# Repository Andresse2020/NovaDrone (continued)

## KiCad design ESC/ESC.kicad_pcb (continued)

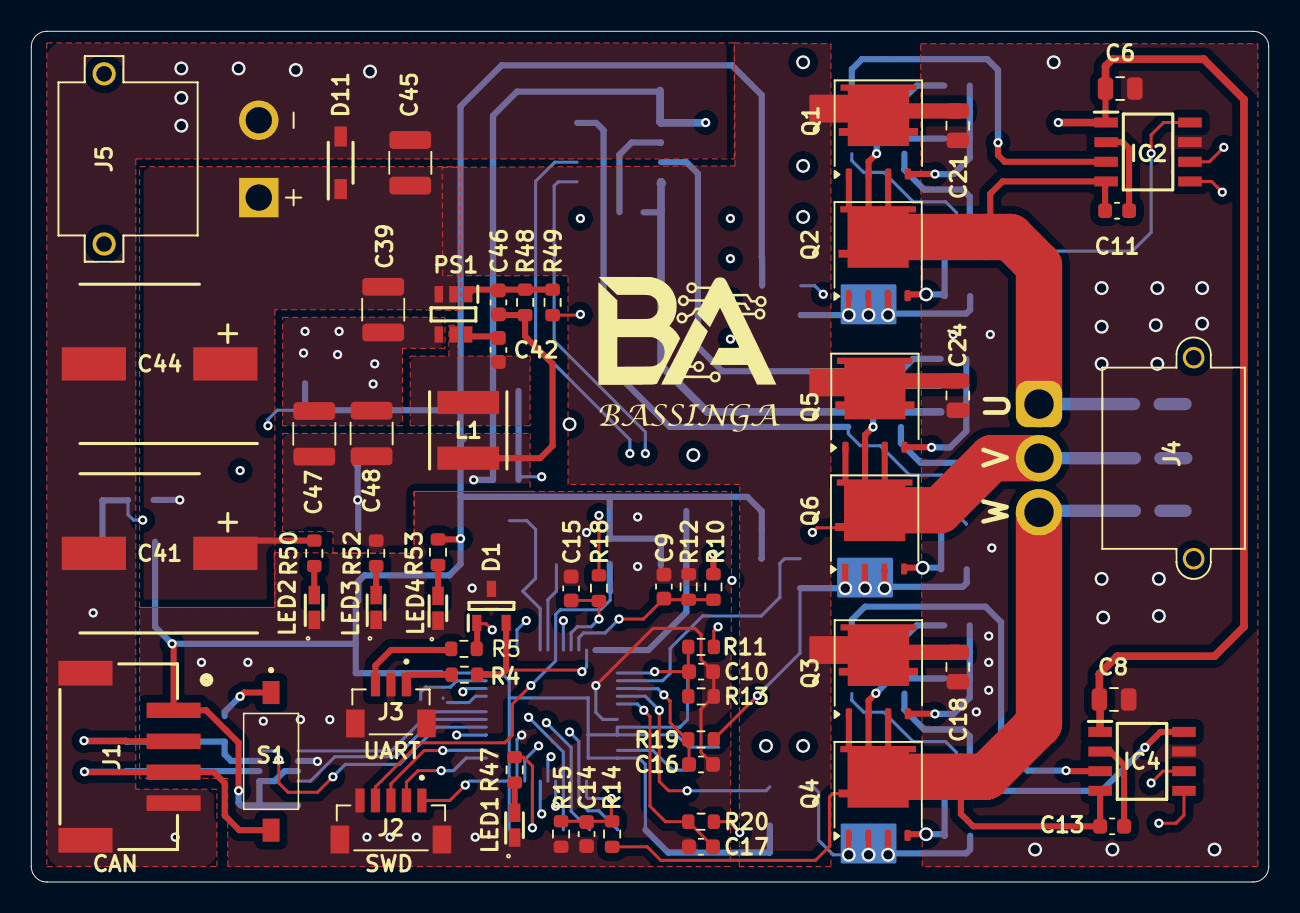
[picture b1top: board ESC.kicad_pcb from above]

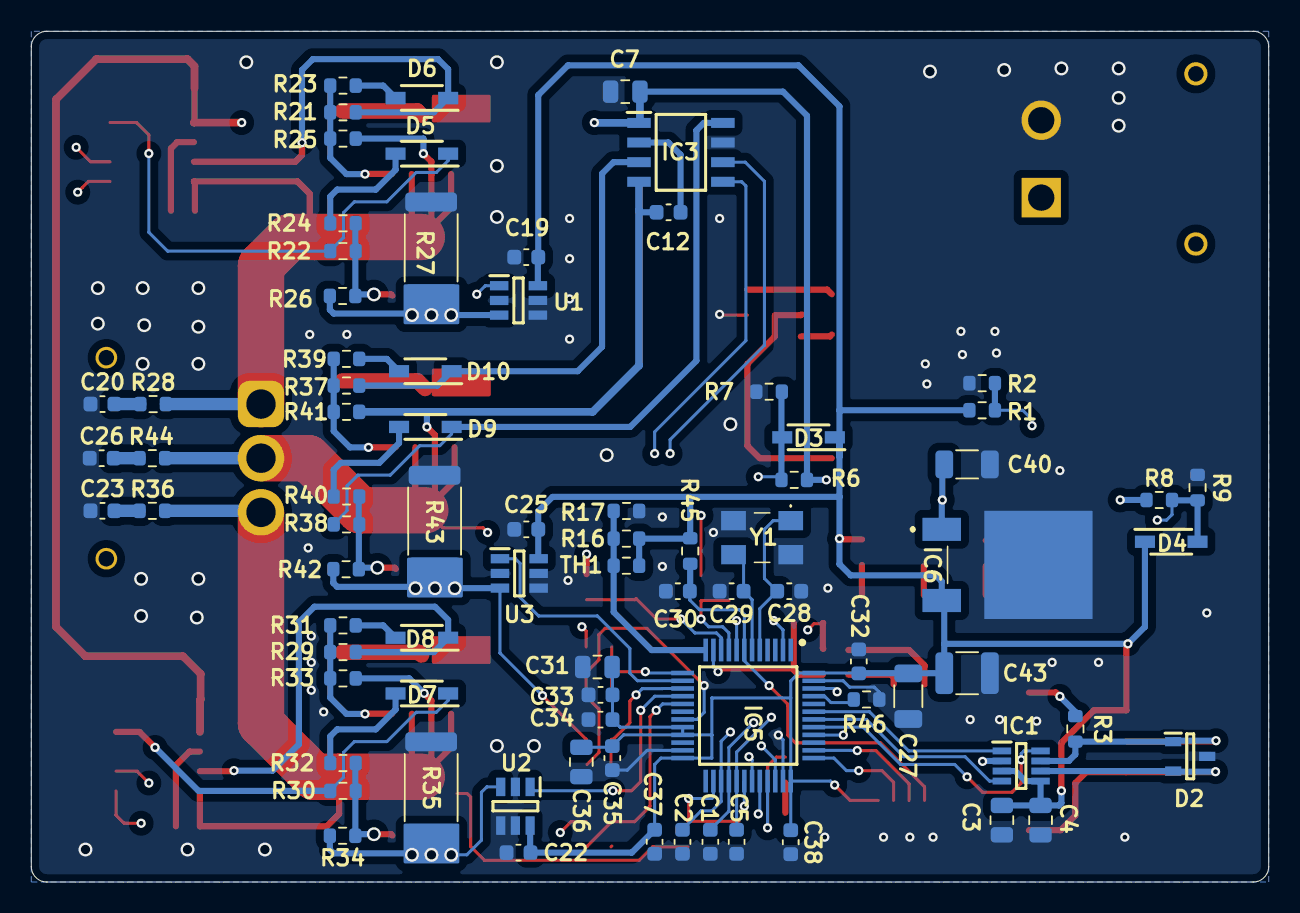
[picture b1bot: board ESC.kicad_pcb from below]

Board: 4 copper layers, 80.0 x 55.0 mm, 140 parts (80 on the bottom side), 77 nets.

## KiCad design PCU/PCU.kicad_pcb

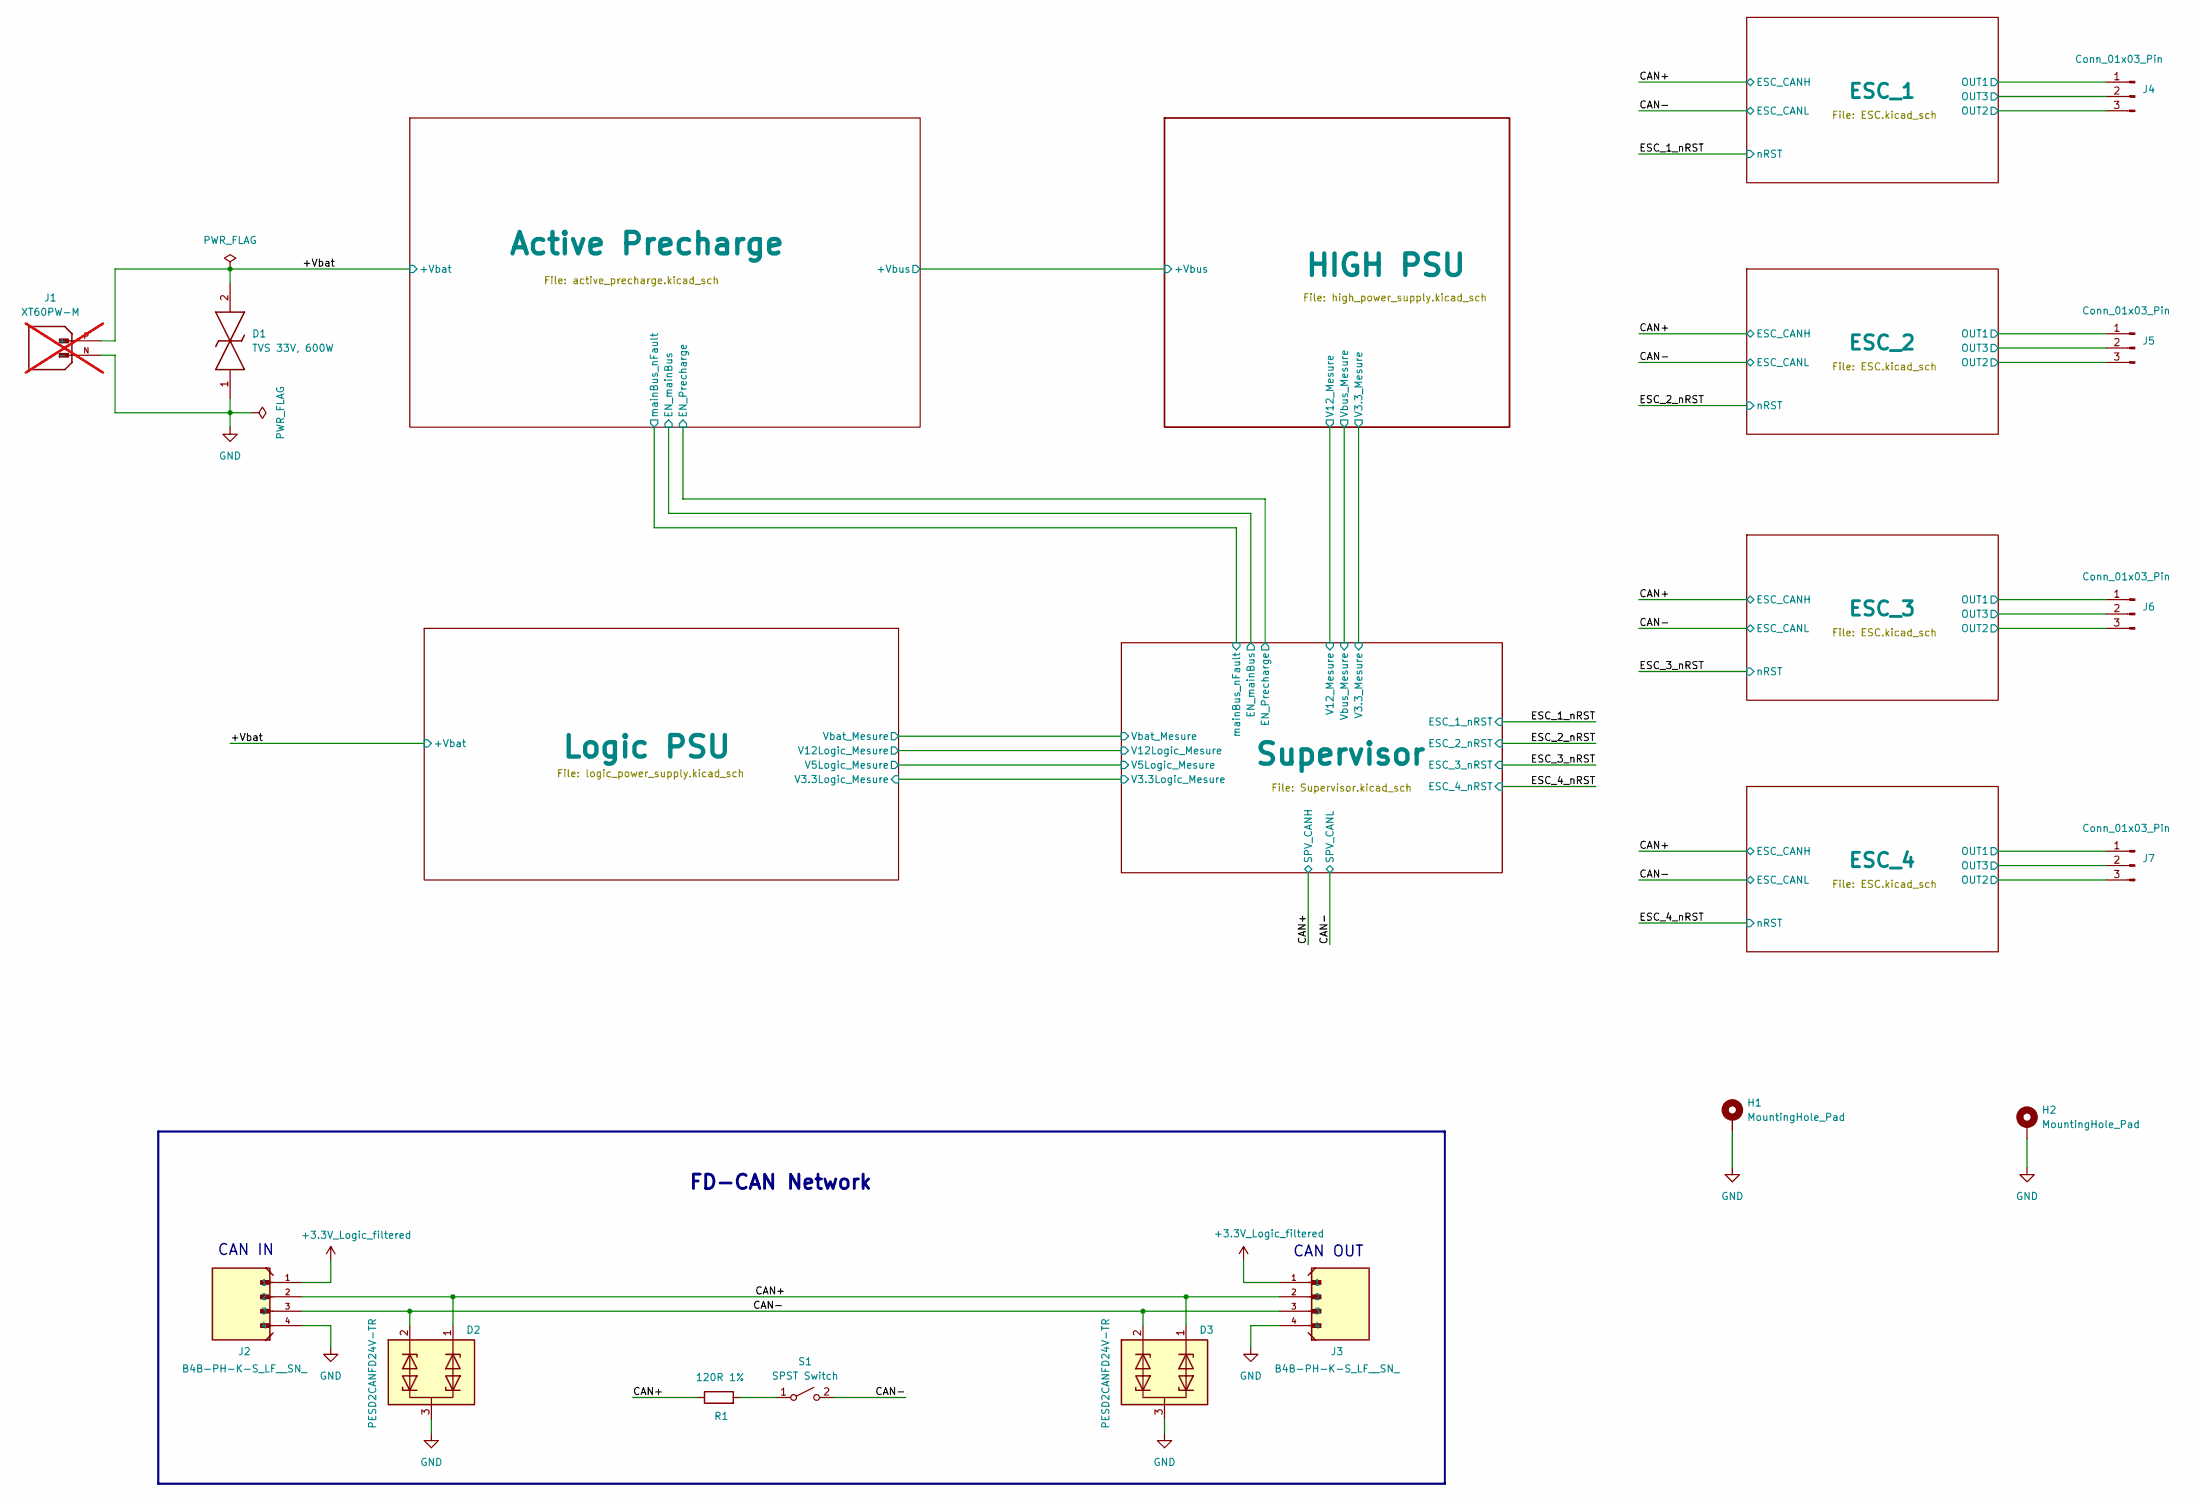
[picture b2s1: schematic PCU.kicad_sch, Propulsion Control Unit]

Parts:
D1: TVS 33V, 600W; DIONM5436X244N; Mouser Part Number 652-SMBJ33CA
D2, D3: PESD2CANFD24V-TR; SOT95P230X110-3N; Mouser Part Number 771-PESD2CANFD24V-TR
H1, H2: MountingHole_Pad; MountingHole_2.2mm_M2_DIN965_Pad
J1: XT60PW-M; AMASS_XT60PW-M; PARTREV V1.2; not fitted
J2, J3: B4B-PH-K-S_LF__SN_; JST_B4B-PH-K-S_LF__SN_
J4, J5, J6, J7: Conn_01x03_Pin; SolderWire-0.75sqmm_1x03_P4.8mm_D1.25mm_OD2.3mm
R1: 120R 1%; R_0603_1608Metric; Manufacturer_Part_Number AC0603FR-07120RL
S1: SPST Switch; DS04254201BKSMT; Mouser Part Number 490-DS04254201BK-SMT

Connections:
+3.3V_Logic_filtered: J2.1, J3.1; also elsewhere on the board
/+Vbat: D1.2, J1.P (+); also elsewhere on the board
/CAN+: D2.1, D3.1, J2.2, J3.2, R1.1; also elsewhere on the board
/CAN-: D2.2, D3.2, J2.3, J3.3, S1.2; also elsewhere on the board
/ESC_1/OUT1: J4.1; also elsewhere on the board
/ESC_1/OUT2: J4.3; also elsewhere on the board
/ESC_1/OUT3: J4.2; also elsewhere on the board
/ESC_2/OUT1: J5.1; also elsewhere on the board
/ESC_2/OUT2: J5.3; also elsewhere on the board
/ESC_2/OUT3: J5.2; also elsewhere on the board
/ESC_3/OUT1: J6.1; also elsewhere on the board
/ESC_3/OUT2: J6.3; also elsewhere on the board
/ESC_3/OUT3: J6.2; also elsewhere on the board
/ESC_4/OUT1: J7.1; also elsewhere on the board
/ESC_4/OUT2: J7.3; also elsewhere on the board
/ESC_4/OUT3: J7.2; also elsewhere on the board
GND: D1.1, D2.3, D3.3, H1.1, H2.1, J1.N (-), J2.4, J3.4; also elsewhere on the board
unnamed: R1.2, S1.1

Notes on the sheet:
CAN IN
FD-CAN Network
CAN OUT

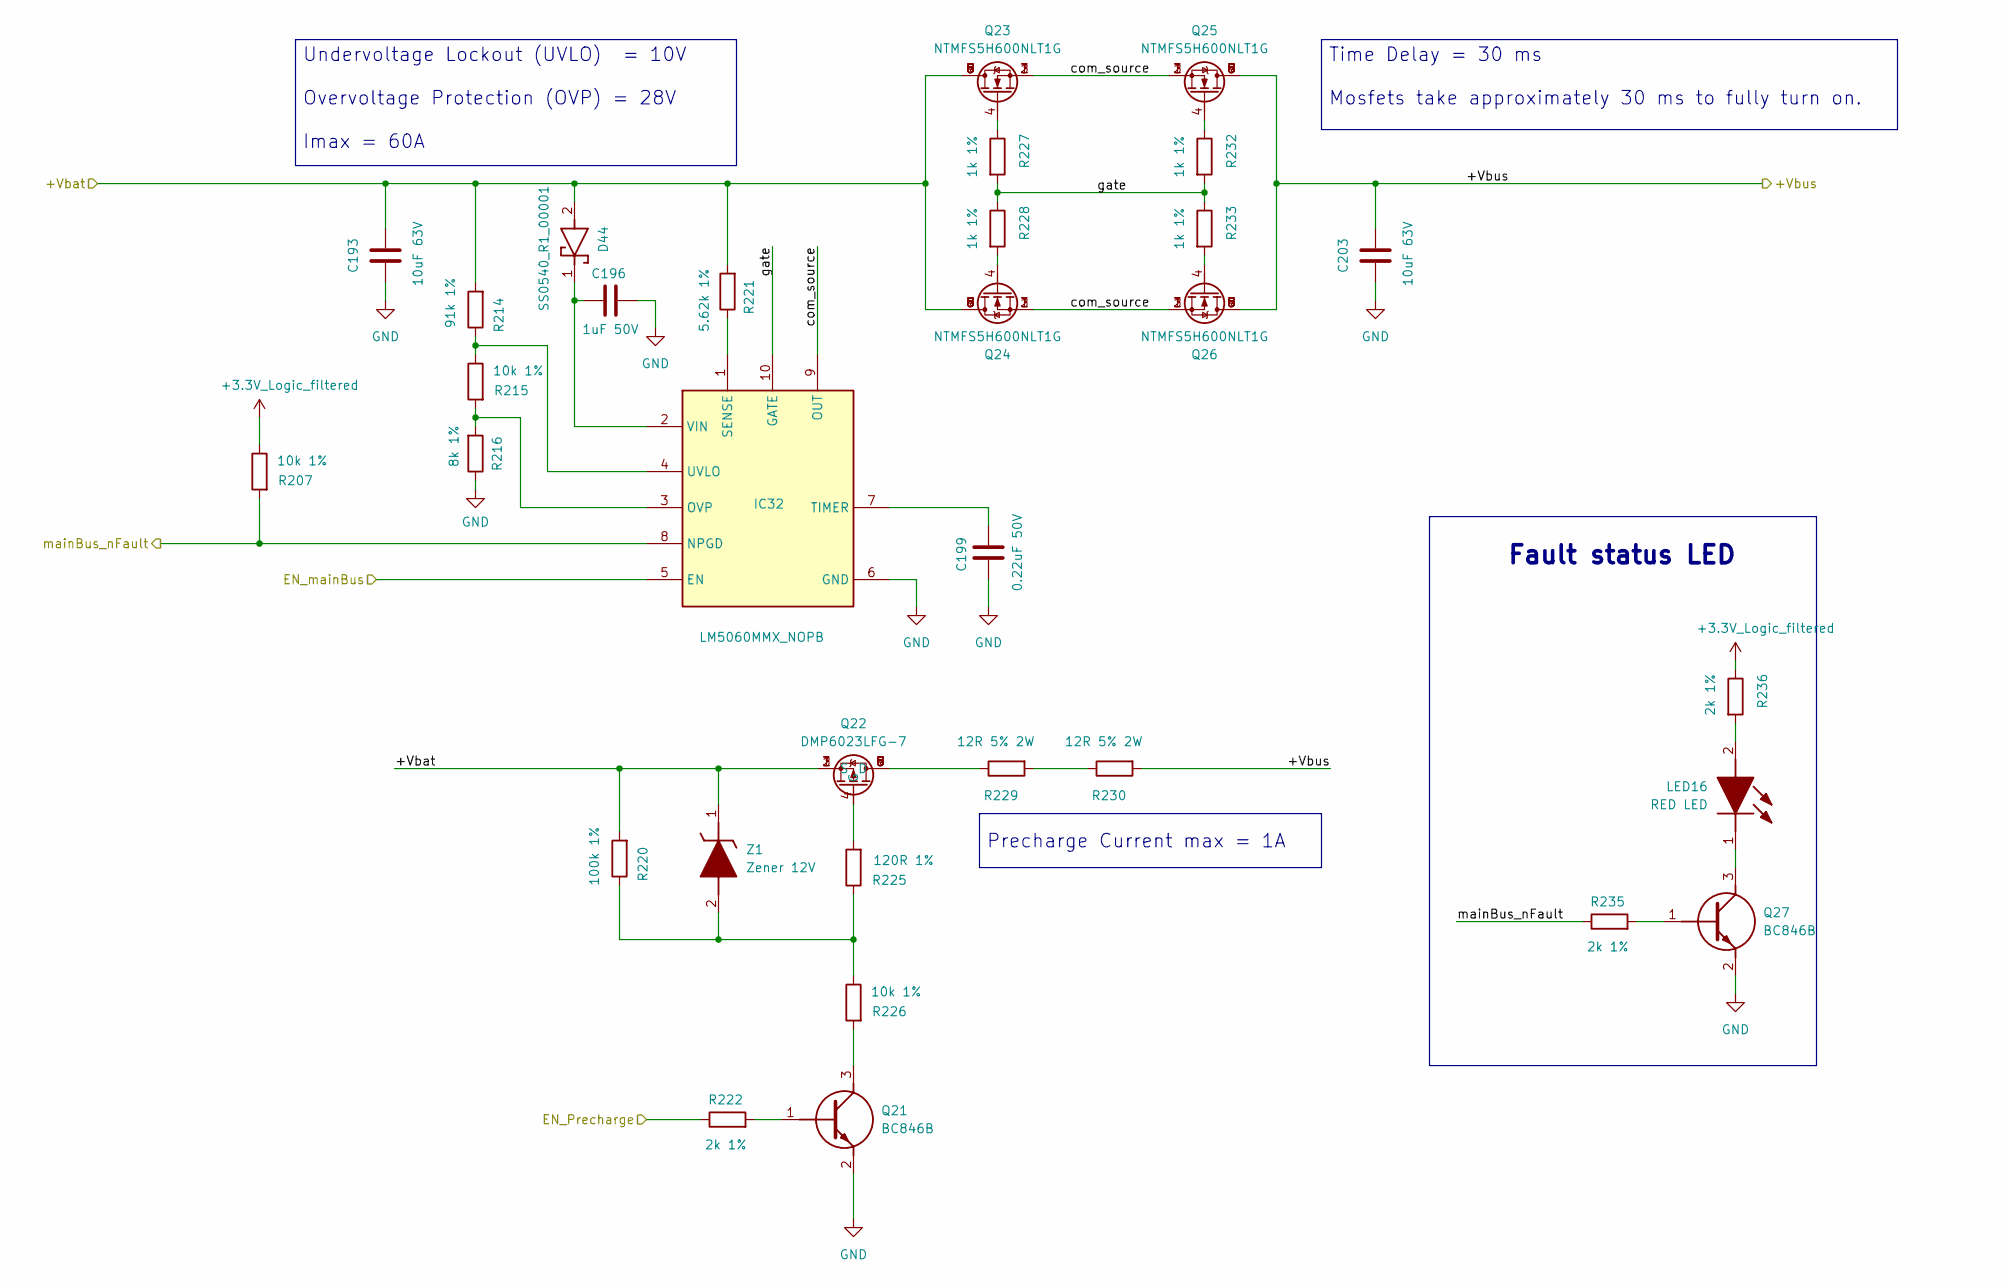
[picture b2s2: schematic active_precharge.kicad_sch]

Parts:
C193, C203: 10uF 63V; C_1210_3225Metric; Manufacturer_Part_Number CL32B106KMVNNWE
C196: 1uF 50V; C_0805_2012Metric; Manufacturer_Part_Number CL21B105KBFNNNE
C199: 0.22uF 50V; C_0603_1608Metric; Manufacturer_Part_Number CL10B224KB8NNNC
D44: SS0540_R1_00001; SOD3816X135N; Mouser Part Number 241-SS0540_R1_00001
IC32: LM5060MMX_NOPB; SOP50P490X110-10N; Mouser Part Number 926-LM5060MMX/NOPB
LED16: RED LED; LEDM168X80N; Manufacturer_Part_Number APHD1608LSURCK
Q21, Q27: BC846B; SOT95P230X110-3N; Mouser Part Number 637-BC846B
Q22: DMP6023LFG-7; DMP4013LFG7; Mouser Part Number 621-DMP6023LFG-7
Q23, Q24, Q25, Q26: NTMFS5H600NLT1G; Mouser Part Number 863-NTMFS5H600NLT1G
R207, R215, R226: 10k 1%; R_0603_1608Metric; Manufacturer_Part_Number AF0603FR-0710KL
R214: 91k 1%; R_0603_1608Metric; Manufacturer_Part_Number RT0603BRD0791KL
R216: 8k 1%; R_0603_1608Metric; Manufacturer_Part_Number RT0603BRE078KL
R220: 100k 1%; R_0603_1608Metric; Manufacturer_Part_Number AT0603FRE07100KL
R221: 5.62k 1%; R_0603_1608Metric; Manufacturer_Part_Number RC0603FR-135K62L
R222, R235, R236: 2k 1%; R_0603_1608Metric; Manufacturer_Part_Number RE0603FRE072KL
R225: 120R 1%; R_0603_1608Metric; Manufacturer_Part_Number AC0603FR-07120RL
R227, R228, R232, R233: 1k 1%; R_0603_1608Metric; Manufacturer_Part_Number RT0603FRE071KL
R229, R230: 12R 5% 2W; R_2512_6332Metric; Manufacturer_Part_Number CRGH2512J12R
Z1: Zener 12V; SOD3716X135N; Mouser Part Number 863-MMSZ12T1G

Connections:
+3.3V_Logic_filtered: R207.1, R236.1; also elsewhere on the board
+Vbus: C203.2, Q25.5, Q25.6, Q25.7, Q25.8, Q25.9, Q26.5, Q26.6, Q26.7, Q26.8, Q26.9, R230.2; also elsewhere on the board
/+Vbat: C193.2, D44.2 (A), Q22.1 (S), Q22.2 (S), Q22.3 (S), Q23.5, Q23.6, Q23.7, Q23.8, Q23.9, Q24.5, Q24.6, Q24.7, Q24.8, Q24.9, R214.2, R220.2, R221.2, Z1.1 (K); also elsewhere on the board
/Active Precharge/EN_Precharge: R222.1; also elsewhere on the board
/Active Precharge/EN_mainBus: IC32.5 (EN); also elsewhere on the board
/Active Precharge/com_source: IC32.9 (OUT), Q23.1, Q23.2, Q23.3, Q24.1, Q24.2, Q24.3, Q25.1, Q25.2, Q25.3, Q26.1, Q26.2, Q26.3
/Active Precharge/gate: IC32.10 (GATE), R227.2, R228.1, R232.2, R233.1
/Active Precharge/mainBus_nFault: IC32.8 (NPGD), R207.2, R235.1; also elsewhere on the board
GND: C193.1, C196.2, C199.1, C203.1, IC32.6 (GND), Q21.2 (E), Q27.2 (E), R216.1; also elsewhere on the board
unnamed: C196.1, D44.1 (K), IC32.2 (VIN)
unnamed: IC32.3 (OVP), R215.2, R216.2
unnamed: IC32.1 (SENSE), R221.1
unnamed: C199.2, IC32.7 (TIMER)
unnamed: IC32.4 (UVLO), R214.1, R215.1
unnamed: LED16.2 (A), R236.2
unnamed: LED16.1 (K), Q27.3 (C)
unnamed: Q21.1 (B), R222.2
unnamed: Q21.3 (C), R226.2
unnamed: Q22.5 (D), Q22.6 (D), Q22.7 (D), Q22.8 (D), Q22.9 (D), R229.1
unnamed: Q22.4 (G), R225.2
unnamed: Q23.4, R227.1
unnamed: Q24.4, R228.2
unnamed: Q25.4, R232.1
unnamed: Q26.4, R233.2
unnamed: Q27.1 (B), R235.2
unnamed: R229.2, R230.1
unnamed: R220.1, R225.1, R226.1, Z1.2 (A)

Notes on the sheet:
Fault status LED
Precharge Current max = 1A
Undervoltage Lockout (UVLO) = 10V Overvoltage Protection (OVP) = 28V Imax = 60A
Time Delay = 30 ms Mosfets take approximately 30 ms to fully turn on.

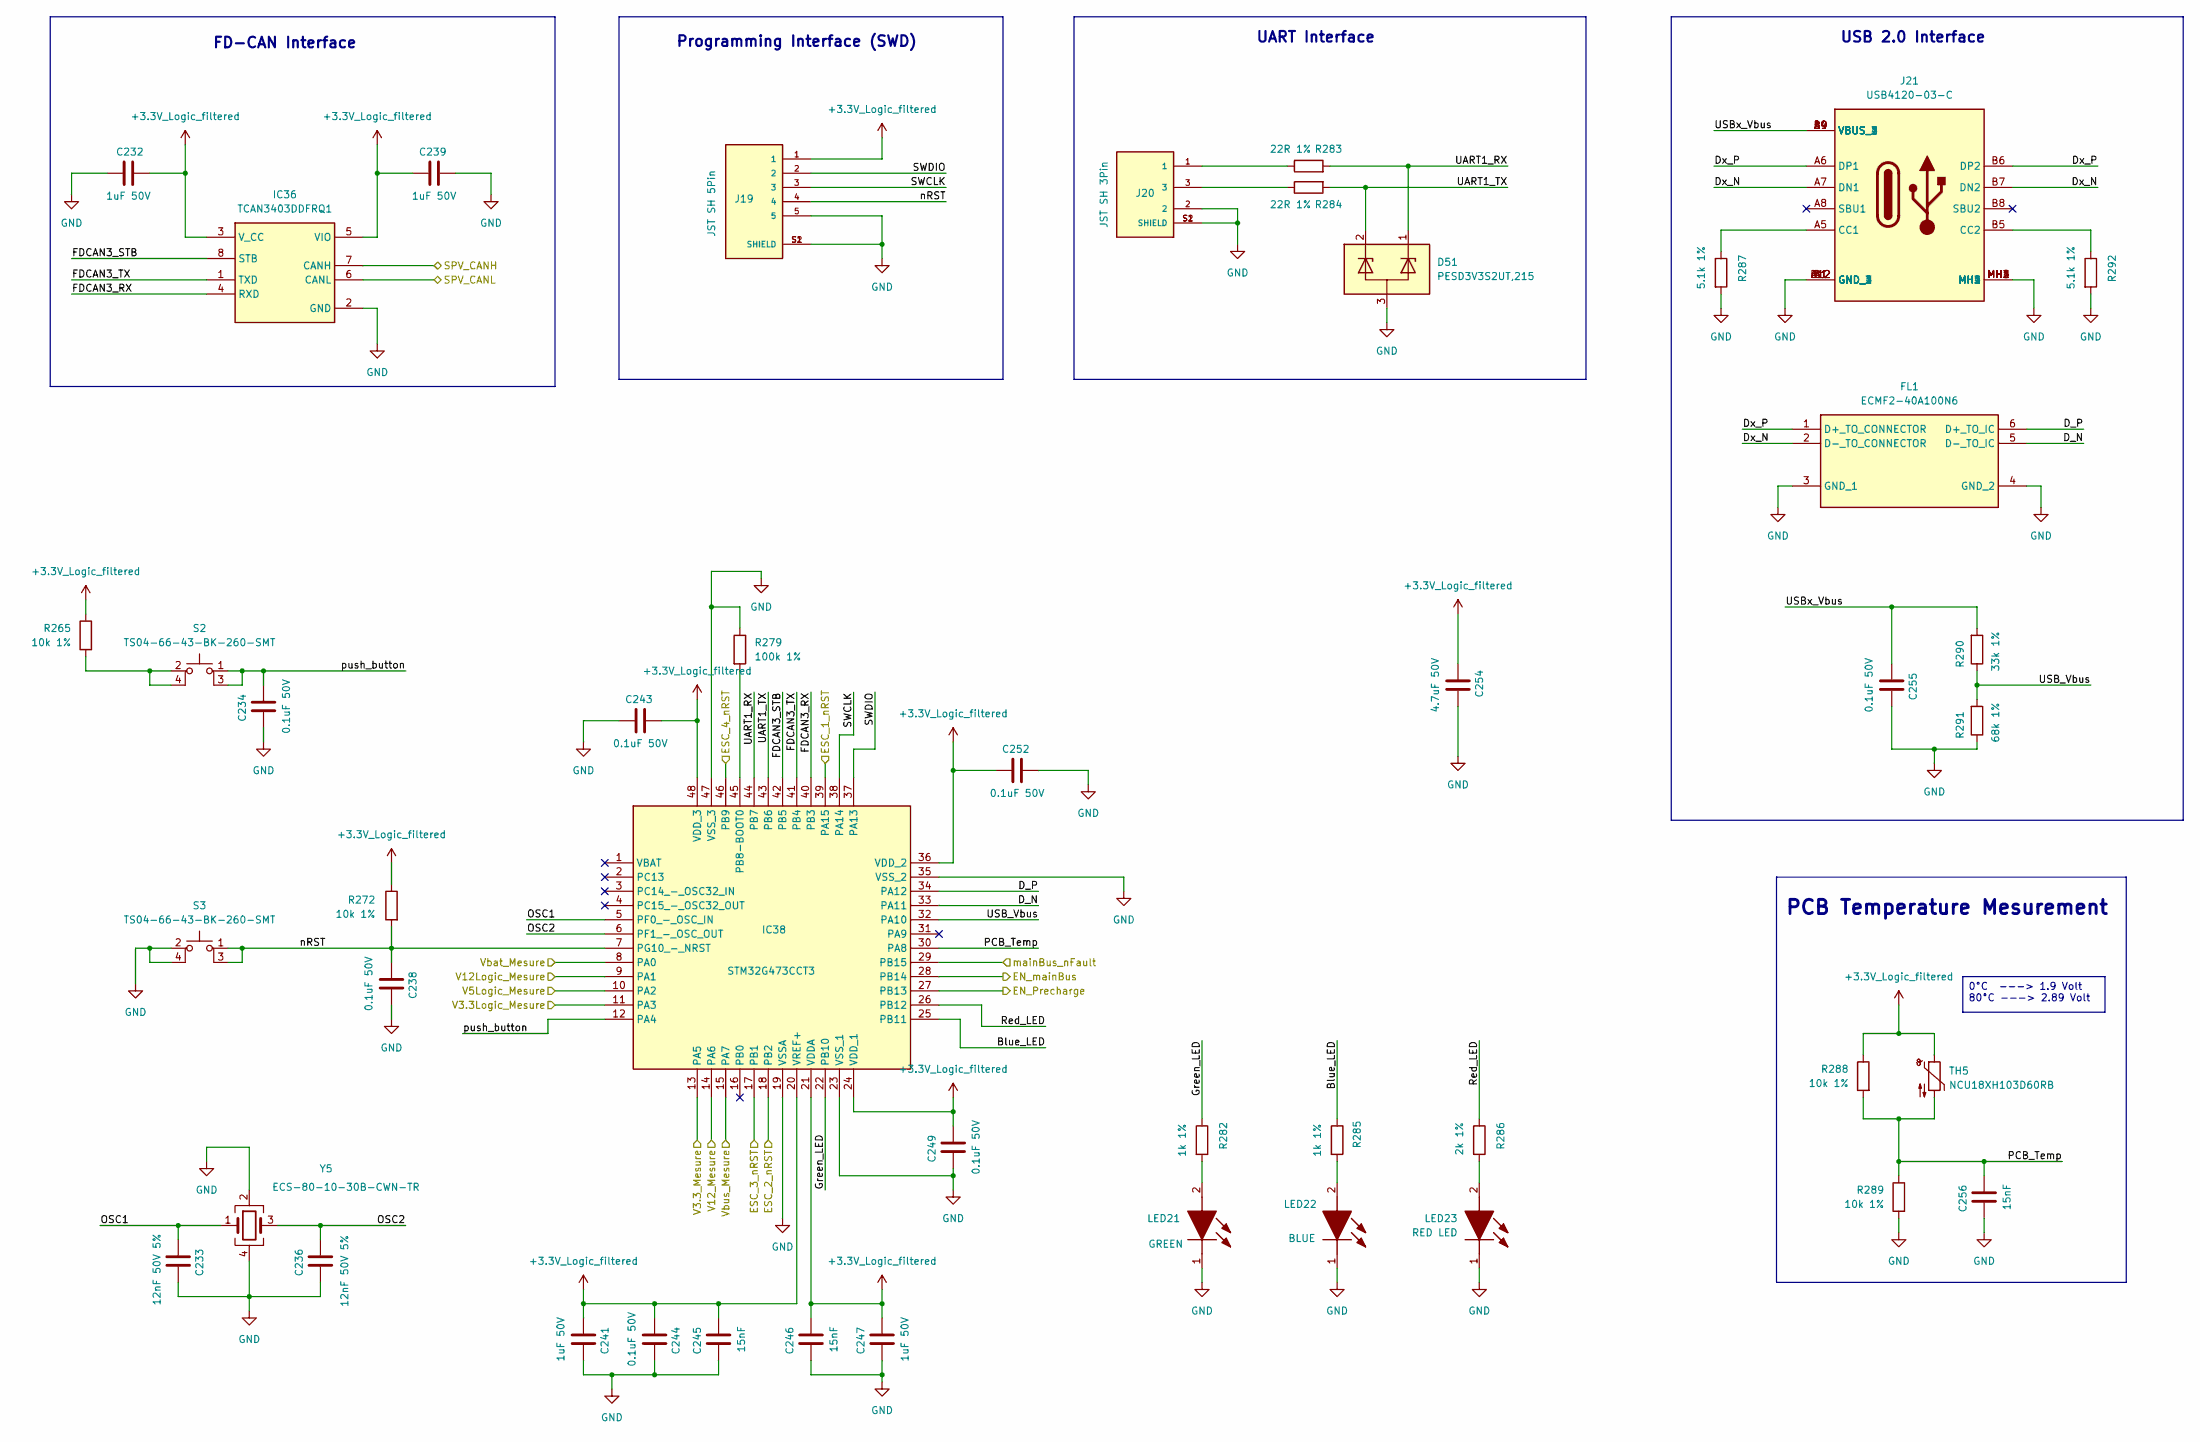
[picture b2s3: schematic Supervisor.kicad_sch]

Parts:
C232, C239, C241, C247: 1uF 50V; C_0805_2012Metric; Manufacturer_Part_Number CL21B105KBFNNNE
C233, C236: 12nF 50V 5%; C_0603_1608Metric; Manufacturer_Part_Number 06035C120J4T2A
C234, C238, C243, C244, C249, C252, C255: 0.1uF 50V; C_0603_1608Metric; Manufacturer_Part_Number CL10B104KB85PNL
C245, C246, C256: 15nF; C_0603_1608Metric; Manufacturer_Part_Number CL10B153KB8NNNC
C254: 4.7uF 50V; C_1206_3216Metric; Manufacturer_Part_Number CL31B475KBHNFNE
D51: PESD3V3S2UT,215; SOT95P230X110-3N; Mouser Part Number 771-PESD3V3S2UT-T/R
FL1: ECMF2-40A100N6; ECMF240A100N6; Mouser Part Number 511-ECMF2-40A100N6
IC36: TCAN3403DDFRQ1; SOT65P280X110-8N; Mouser Part Number 595-TCAN3403DDFRQ1
IC38: STM32G473CCT3; QFP50P900X900X160-48N; Mouser Part Number 511-STM32G473CCT3
J19: JST SH 5Pin; JST_BM05B-SRSS-TB_LF__SN_; PARTREV N/A
J20: JST SH 3Pin; JST_BM03B-SRSS-TB_LF__SN_; PARTREV N/A
J21: USB4120-03-C; USB412003C; Mouser Part Number 640-USB4120-03-C
LED21: GREEN; LEDM168X80N; Mouser Part Number 604-APHD1608LZGCK
LED22: BLUE; LEDM168X80N; Mouser Part Number 604-APHD1608LQBCD
LED23: RED LED; LEDM168X80N; Manufacturer_Part_Number APHD1608LSURCK
R265, R272, R288, R289: 10k 1%; R_0603_1608Metric; Manufacturer_Part_Number AF0603FR-0710KL
R279: 100k 1%; R_0603_1608Metric; Manufacturer_Part_Number AT0603FRE07100KL
R282, R285: 1k 1%; R_0603_1608Metric; Manufacturer_Part_Number RT0603FRE071KL
R283, R284: 22R 1%; R_0603_1608Metric; Manufacturer_Part_Number RT0603FRD0722RL
R286: 2k 1%; R_0603_1608Metric; Manufacturer_Part_Number RE0603FRE072KL
R287, R292: 5.1k 1%; R_0603_1608Metric; Manufacturer_Part_Number RC0603FR-075K1P
R290: 33k 1%; R_0603_1608Metric; Manufacturer_Part_Number AC0603FR-1333KL
R291: 68k 1%; R_0603_1608Metric; Manufacturer_Part_Number RC0603FR-1068KL
S2, S3: TS04-66-43-BK-260-SMT; TS046643BK260SMT; Mouser Part Number 179-TS046643BK260SMT
TH5: NCU18XH103D60RB; R_0603_1608Metric; Manufacturer_Part_Number NCU18XH103D60RB
Y5: ECS-80-10-30B-CWN-TR; ECS801830BAGNTR; Mouser Part Number 520-80-10-30B-CWNT

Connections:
+3.3V_Logic_filtered: C232.1, C239.1, C241.2, C243.2, C244.2, C245.2, C246.2, C247.2, C249.2, C252.1, C254.1, IC36.3 (V_CC), IC36.5 (VIO), IC38.20 (VREF+), IC38.21 (VDDA), IC38.24 (VDD_1), IC38.36 (VDD_2), IC38.48 (VDD_3), J19.1, R265.1, R272.1, R288.1, TH5.1; also elsewhere on the board
/Active Precharge/EN_Precharge: IC38.27 (PB13); also elsewhere on the board
/Active Precharge/EN_mainBus: IC38.28 (PB14); also elsewhere on the board
/Active Precharge/mainBus_nFault: IC38.29 (PB15); also elsewhere on the board
/CAN+: IC36.7 (CANH); also elsewhere on the board
/CAN-: IC36.6 (CANL); also elsewhere on the board
/ESC_1_nRST: IC38.39 (PA15); also elsewhere on the board
/ESC_2_nRST: IC38.18 (PB2); also elsewhere on the board
/ESC_3_nRST: IC38.17 (PB1); also elsewhere on the board
/ESC_4_nRST: IC38.46 (PB9); also elsewhere on the board
/HIGH PSU/V3.3_Mesure: IC38.13 (PA5); also elsewhere on the board
/HIGH PSU/V12_Mesure: IC38.14 (PA6); also elsewhere on the board
/HIGH PSU/Vbus_Mesure: IC38.15 (PA7); also elsewhere on the board
/Logic PSU/V3.3Logic_Mesure: IC38.11 (PA3); also elsewhere on the board
/Logic PSU/V5Logic_Mesure: IC38.10 (PA2); also elsewhere on the board
/Logic PSU/V12Logic_Mesure: IC38.9 (PA1); also elsewhere on the board
/Logic PSU/Vbat_Mesure: IC38.8 (PA0); also elsewhere on the board
/Supervisor/Blue_LED: IC38.25 (PB11), R285.1
/Supervisor/D_N: FL1.5 (D-_TO_IC), IC38.33 (PA11)
/Supervisor/D_P: FL1.6 (D+_TO_IC), IC38.34 (PA12)
/Supervisor/Dx_N: FL1.2 (D-_TO_CONNECTOR), J21.A7 (DN1), J21.B7 (DN2)
/Supervisor/Dx_P: FL1.1 (D+_TO_CONNECTOR), J21.A6 (DP1), J21.B6 (DP2)
/Supervisor/FDCAN3_RX: IC36.4 (RXD), IC38.40 (PB3)
/Supervisor/FDCAN3_STB: IC36.8 (STB), IC38.42 (PB5)
/Supervisor/FDCAN3_TX: IC36.1 (TXD), IC38.41 (PB4)
/Supervisor/Green_LED: IC38.22 (PB10), R282.1
/Supervisor/OSC1: C233.2, IC38.5 (PF0_-_OSC_IN), Y5.1
/Supervisor/OSC2: C236.2, IC38.6 (PF1_-_OSC_OUT), Y5.3
/Supervisor/PCB_Temp: C256.2, IC38.30 (PA8), R288.2, R289.1, TH5.2
/Supervisor/Red_LED: IC38.26 (PB12), R286.1
/Supervisor/SWCLK: IC38.38 (PA14), J19.3
/Supervisor/SWDIO: IC38.37 (PA13), J19.2
/Supervisor/UART1_RX: D51.1, IC38.44 (PB7), R283.2
/Supervisor/UART1_TX: D51.2, IC38.43 (PB6), R284.2
/Supervisor/USB_Vbus: IC38.32 (PA10), R290.1, R291.2
/Supervisor/USBx_Vbus: C255.2, J21.A4 (VBUS_1), J21.A9 (VBUS_2), J21.B4 (VBUS_3), J21.B9 (VBUS_4), R290.2
/Supervisor/nRST: C238.2, IC38.7 (PG10_-_NRST), J19.4, R272.2, S3.1, S3.3
/Supervisor/push_button: C234.2, IC38.12 (PA4), S2.1, S2.3
GND: C232.2, C233.1, C234.1, C236.1, C238.1, C239.2, C241.1, C243.1, C244.1, C245.1, C246.1, C247.1, C249.1, C252.2, C254.2, C255.1, C256.1, D51.3, FL1.3 (GND_1), FL1.4 (GND_2), IC36.2 (GND), IC38.19 (VSSA), IC38.23 (VSS_1), IC38.35 (VSS_2), IC38.47 (VSS_3), J19.5, J19.S1 (SHIELD), J19.S2 (SHIELD), J20.2, J20.S1 (SHIELD), J20.S2 (SHIELD), J21.A1 (GND_1), J21.A12 (GND_2), J21.B1 (GND_3), J21.B12 (GND_4), J21.MH1, J21.MH2, J21.MH3, J21.MH4, LED21.1 (K), LED22.1 (K), LED23.1 (K), R279.1, R287.2, R289.2, R291.1, R292.2, S3.2, S3.4, Y5.2, Y5.4; also elsewhere on the board
unnamed: IC38.45 (PB8-BOOT0), R279.2
unnamed: J20.1, R283.1
unnamed: J20.3, R284.1
unnamed: J21.A5 (CC1), R287.1
unnamed: J21.B5 (CC2), R292.1
unnamed: LED21.2 (A), R282.2
unnamed: LED22.2 (A), R285.2
unnamed: LED23.2 (A), R286.2
unnamed: R265.2, S2.2, S2.4

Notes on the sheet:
Programming Interface (SWD)
USB 2.0 Interface
FD-CAN Interface
UART Interface
PCB Temperature Mesurement
0°C ---> 1.9 Volt 80°C ---> 2.89 Volt
